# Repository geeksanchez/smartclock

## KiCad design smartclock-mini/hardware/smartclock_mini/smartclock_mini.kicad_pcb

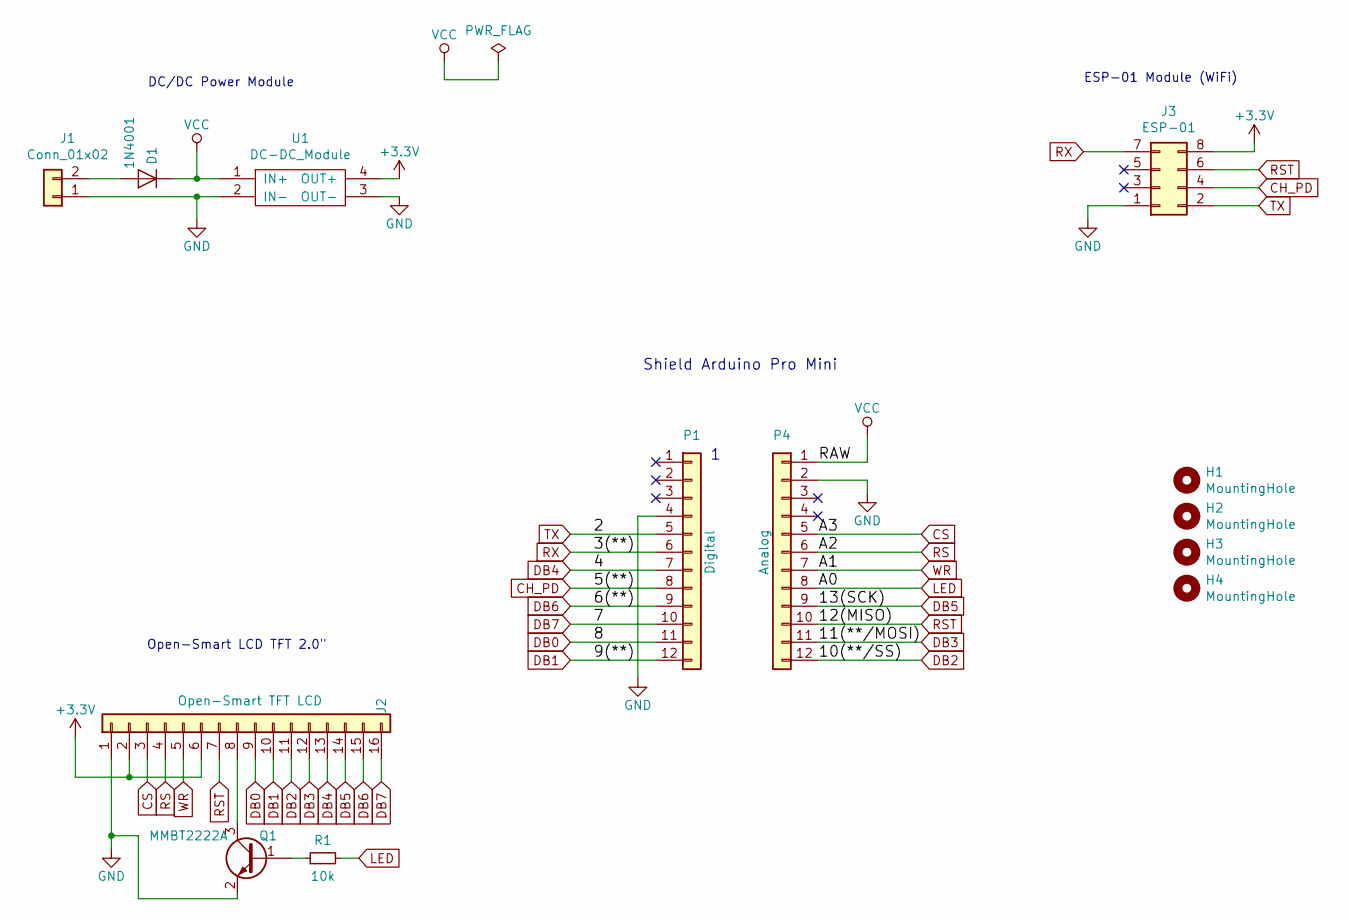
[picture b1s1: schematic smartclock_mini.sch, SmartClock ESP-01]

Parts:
D1: 1N4001; D_A-405_P7.62mm_Horizontal
H1, H2, H3, H4: MountingHole; MountingHole_3.2mm_M3
J1: Conn_01x02; BOR5.0-2
J2: Open-Smart TFT LCD; LCD_TFT_2_00
J3: ESP-01; ESP-01_Module
P1: Digital; Socket_Strip_Arduino_1x12
P4: Analog; Socket_Strip_Arduino_1x12
Q1: MMBT2222A; SOT-23_Handsoldering
R1: 10k; R_Axial_DIN0207_L6.3mm_D2.5mm_P7.62mm_Horizontal
U1: DC-DC_Module; LM2596_DC-DC_Module

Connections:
+3V3: J2.2, J2.6, J3.8, U1.4 (OUT+)
CH_PD: J3.4, P1.8
CS: J2.3, P4.5
DB0: J2.9, P1.11
DB1: J2.10, P1.12
DB2: J2.11, P4.12
DB3: J2.12, P4.11
DB4: J2.13, P1.7
DB5: J2.14, P4.9
DB6: J2.15, P1.9
DB7: J2.16, P1.10
GND: J1.1, J2.1, J3.1, P1.4, P4.2, Q1.2 (E), U1.2 (IN-), U1.3 (OUT-)
LED: P4.8, R1.2
unnamed: D1.2 (A), J1.2
unnamed: J2.8, Q1.3 (C)
unnamed: Q1.1 (B), R1.1
RS: J2.4, P4.6
RST: J2.7, J3.6, P4.10
RX: J3.7, P1.6
TX: J3.2, P1.5
VCC: D1.1 (K), P4.1, U1.1 (IN+)
WR: J2.5, P4.7

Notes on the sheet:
Shield Arduino Pro Mini
ESP-01 Module (WiFi)
Open-Smart LCD TFT 2.0"
DC/DC Power Module

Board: 2 copper layers, 13 parts (1 on the bottom side), 22 nets, no tracks yet.

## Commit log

2020-10-20 Inicio de git
2020-10-21 Ajustes de la rejilla de corte de acuerdo a las dimensiones de la tarjeta
2020-10-21 Bloqueo de modificaciones en el diseño.
2020-10-23 Se agrega el icono de reloj de arena. La clase matrixtask se especializa en visualización. Se adiciona una nueva clase smartclocktask para funciones varias. Se ajusta el main para incluir la nueva cl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
    En este ajuste se visualiza el reloj de arena al iniciar el reloj.
2020-10-23 Ajuste del proceso de reinicio. Se ajusta la clase Matrix con la función de borrado de pantalla. Se complementa OTA para notificar por MQTT su activación. Versión 0.10
2020-10-24 Ajustes de matrix
2020-10-24 Solución del problema de visualización de MSG. Faltaba el break en el switch.
2020-10-25 Ajustes del tipo de letra (font3x5)
2020-10-25 Ajustes de visualización de hora y fecha
2020-10-27 Inicio de la version NG del smartclock
2020-11-01 New test code
2020-11-02 Ajustes de visualización y scroll
2020-11-03 Ajustes finales
2020-11-03 Ajuste de la caja de armado
2020-11-03 Versión 0.3 estable
2020-11-04 Modificación de smartclock mini
2020-11-09 Ajustes en mini reloj de acuerdo al modelo del reloj grande
2020-11-10 Implementar scheduler en arduino
2020-11-14 Cambio de imagen para calendario
2021-07-13 Inicio desarrollo de nueva generación de smarclock
2021-07-14 Change functions to callback format
2021-07-14 Adición de NTP ṕara la hora
2021-07-14 frases
2021-08-09 LED addon
